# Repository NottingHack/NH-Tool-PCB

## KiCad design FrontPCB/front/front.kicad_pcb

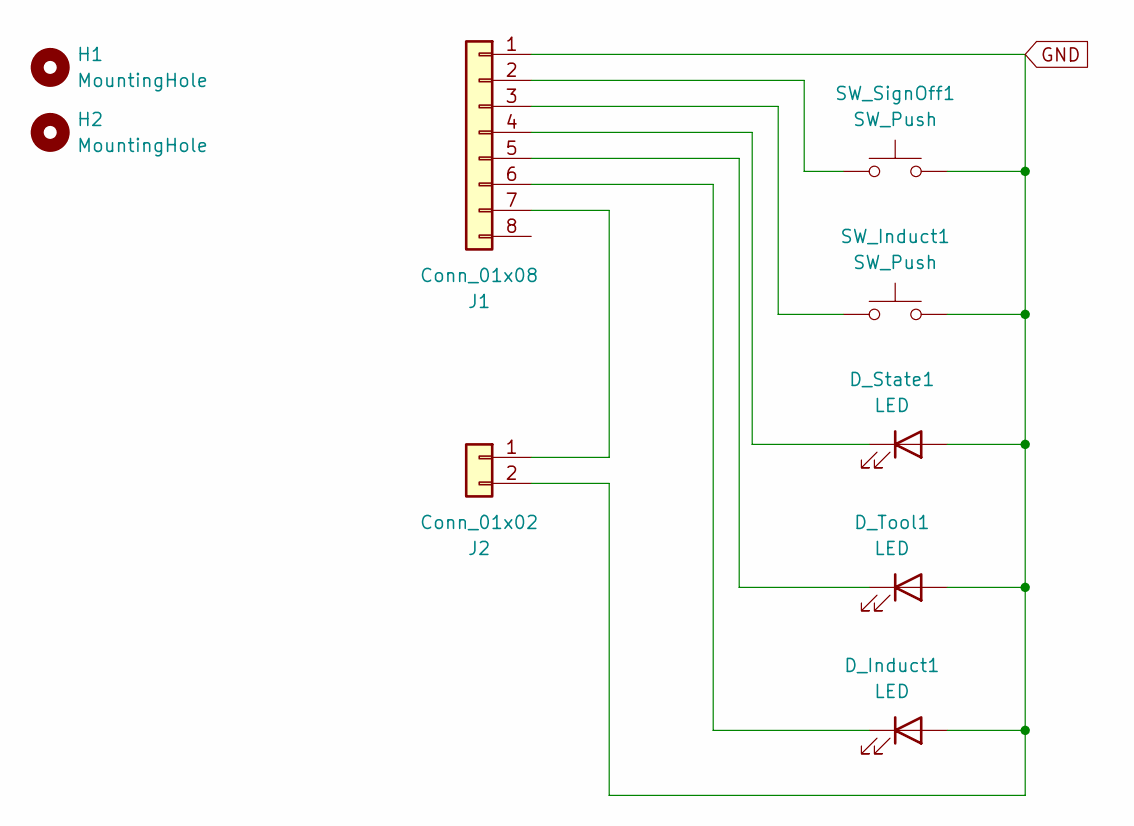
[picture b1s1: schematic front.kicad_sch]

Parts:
D_Induct1: LED; LED_D5.0mm
D_State1: LED; LED_D5.0mm
D_Tool1: LED; LED_D5.0mm
H1, H2: MountingHole; MountingHole_3.2mm_M3
J1: Conn_01x08; PinHeader_1x08_P2.54mm_Horizontal
J2: Conn_01x02; PinHeader_1x02_P2.54mm_Horizontal
SW_Induct1: SW_Push; SW_TH_Tactile_Omron_B3F-10xx
SW_SignOff1: SW_Push; SW_TH_Tactile_Omron_B3F-10xx

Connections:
GND: D_Induct1.2 (A), D_State1.2 (A), D_Tool1.2 (A), J1.1, J2.2, SW_Induct1.2, SW_SignOff1.2
unnamed: D_Induct1.1 (K), J1.6
unnamed: D_State1.1 (K), J1.4
unnamed: D_Tool1.1 (K), J1.5
unnamed: J1.2, SW_SignOff1.1
unnamed: J1.3, SW_Induct1.1
unnamed: J1.7, J2.1

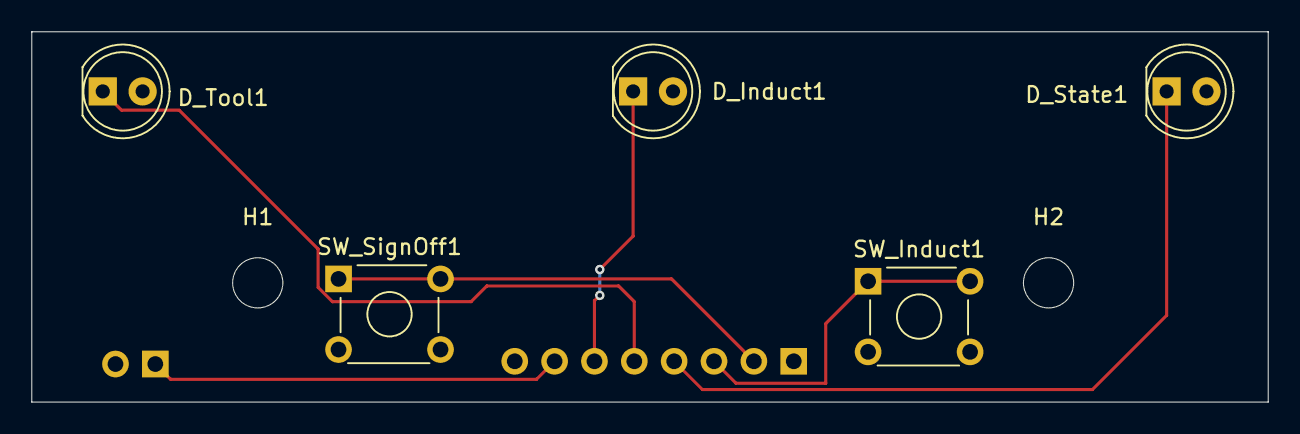
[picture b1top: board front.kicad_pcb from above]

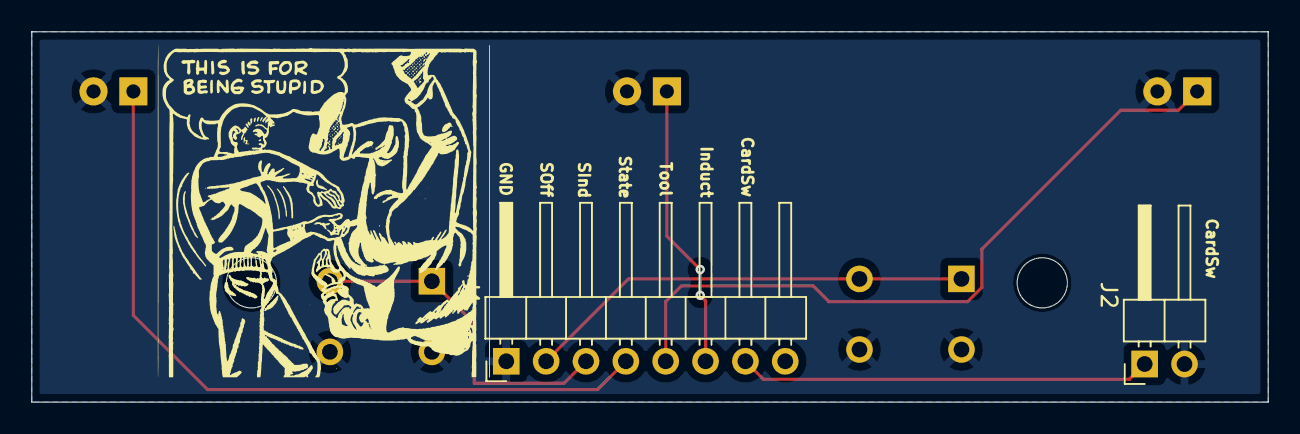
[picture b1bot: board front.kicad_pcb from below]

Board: 2 copper layers, 78.8 x 23.6 mm, 9 parts (2 on the bottom side), 7 nets.

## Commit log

2014-10-08 First push of the PCB
2016-08-17 Add early box design and some WIP board layout
2016-08-21 add laser paths and 3D models for version 2 of the RFID box
2023-05-25 missing v0.2 eagle files
2023-05-25 v0.3 wip pcb files cant remember the changes
2024-08-26 Added a PCB to avoid messy wiring
2024-08-26 Add model for Omron B3F buttons
2024-09-11 Buttons and spacers
2024-12-14 Add alternative box face for heaters 'tap for heating'
